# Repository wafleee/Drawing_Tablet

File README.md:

# Drawing Tablet

I am making a bluetooth drawing tablet that can send images you make on it to your computer. The main audience is people who love digital drawing but cant afford proper hardware like a Ipad and apple pencil or Large drawing pad. 

$\huge\text{Features}$
____________________________________________________________________________________________________________________________________________________________________________________________________________________________
- High quality image export (via BLE or Wifi)
- Multicolor drawing
- Save pictures to ESP32 memory
- Long battery life (3-4 hour, with continuous usage )
- Built in Stylus storage
- Large Screen (2.8 inches)

$\huge\text{Schematic}$
____________________________________________________________________________________________________________________________________________________________________________________________________________________________

The schematic is easy to understand and has neat wiring

$\huge\text{PCB Design }$
____________________________________________________________________________________________________________________________________________________________________________________________________________________________

$\huge\text{BOM }$
____________________________________________________________________________________________________________________________________________________________________________________________________________________________

$\large\text{Price in INR }$

| Ref.       | Qty | Part / Value             | LCSC #        |      Price / pc |
| ---------- | --: | ------------------------ | ------------- | --------------: |
| BT2        |   1 | JST-PH 2-pin             | **C265016**   |           ₹6.41 |
| C1, C4     |   2 | 4.7 µF                   | **C915849**   |          ₹56.46 |
| C5         |   1 | 10 µF                    | **C111896**   |          ₹78.10 |
| C6         |   1 | 0.1 µF                   | **C106148**   |          ₹11.42 |
| C7, C8     |   2 | 1 µF                     | **C91185**    |           ₹3.55 |
| D1, D2, D3 |   3 | Indicator LED            | **C125084**   |           ₹3.95 |
| IC1        |   1 | NCP186 3.3 V LDO         | **C719823**   |          ₹32.75 |
| J1         |   1 | 1×14 female socket       | **C2905420**  |          ₹14.69 |
| J2         |   1 | 1×5 male header          | **C55629812** |           ₹3.69 |
| J3         |   1 | USB-C USB 2.0 receptacle | **C3025063**  |          ₹98.75 |
| R1, R2, R6 |   3 | 470 Ω                    | **C114564**   |           ₹0.51 |
| R3, R4     |   2 | 10 kΩ                    | **C84376**    |           ₹0.63 |
| R5, R10    |   2 | 5.1 kΩ                   | **C728389**   |          ₹2.14  |
| R7         |   1 | 1.5 kΩ                   | **C309587**   |           ₹1.52 |
| R8, R9     |   2 | 10 kΩ                    | **C84376**    |           ₹0.63 |
| SW3, SW4   |   2 | Push button              | **C318884**   |           ₹1.98 |
| U1         |   1 | ESP32-S3-MINI-1-N4       | **C2847294**  |           ₹ 369 |
| U4         |   1 | USB ESD protection       | **C94934**    |          ₹51.26 |
| U5         |   1 | MCP73871                 | **C144351**   |         ₹456.94 |

$\huge\text{Firmware}$

You do not have to add any external software. Just upload the code to the board using a cable and the Arduino ide software will handle everything else.

$\huge\text{CREDITS }$
____________________________________________________________________________________________________________________________________________________________________________________________________________________________

FUSION 360 - https://www.autodesk.com/in/products/fusion-360/overview

KICAD - https://www.kicad.org/

Arduino IDE - https://www.arduino.cc/en/software/

$\large\text{FIRMWARE CREDITS  }$

SPI.h

TFT_eSPI.h  By Bodmer 

Bluetoothserial.h

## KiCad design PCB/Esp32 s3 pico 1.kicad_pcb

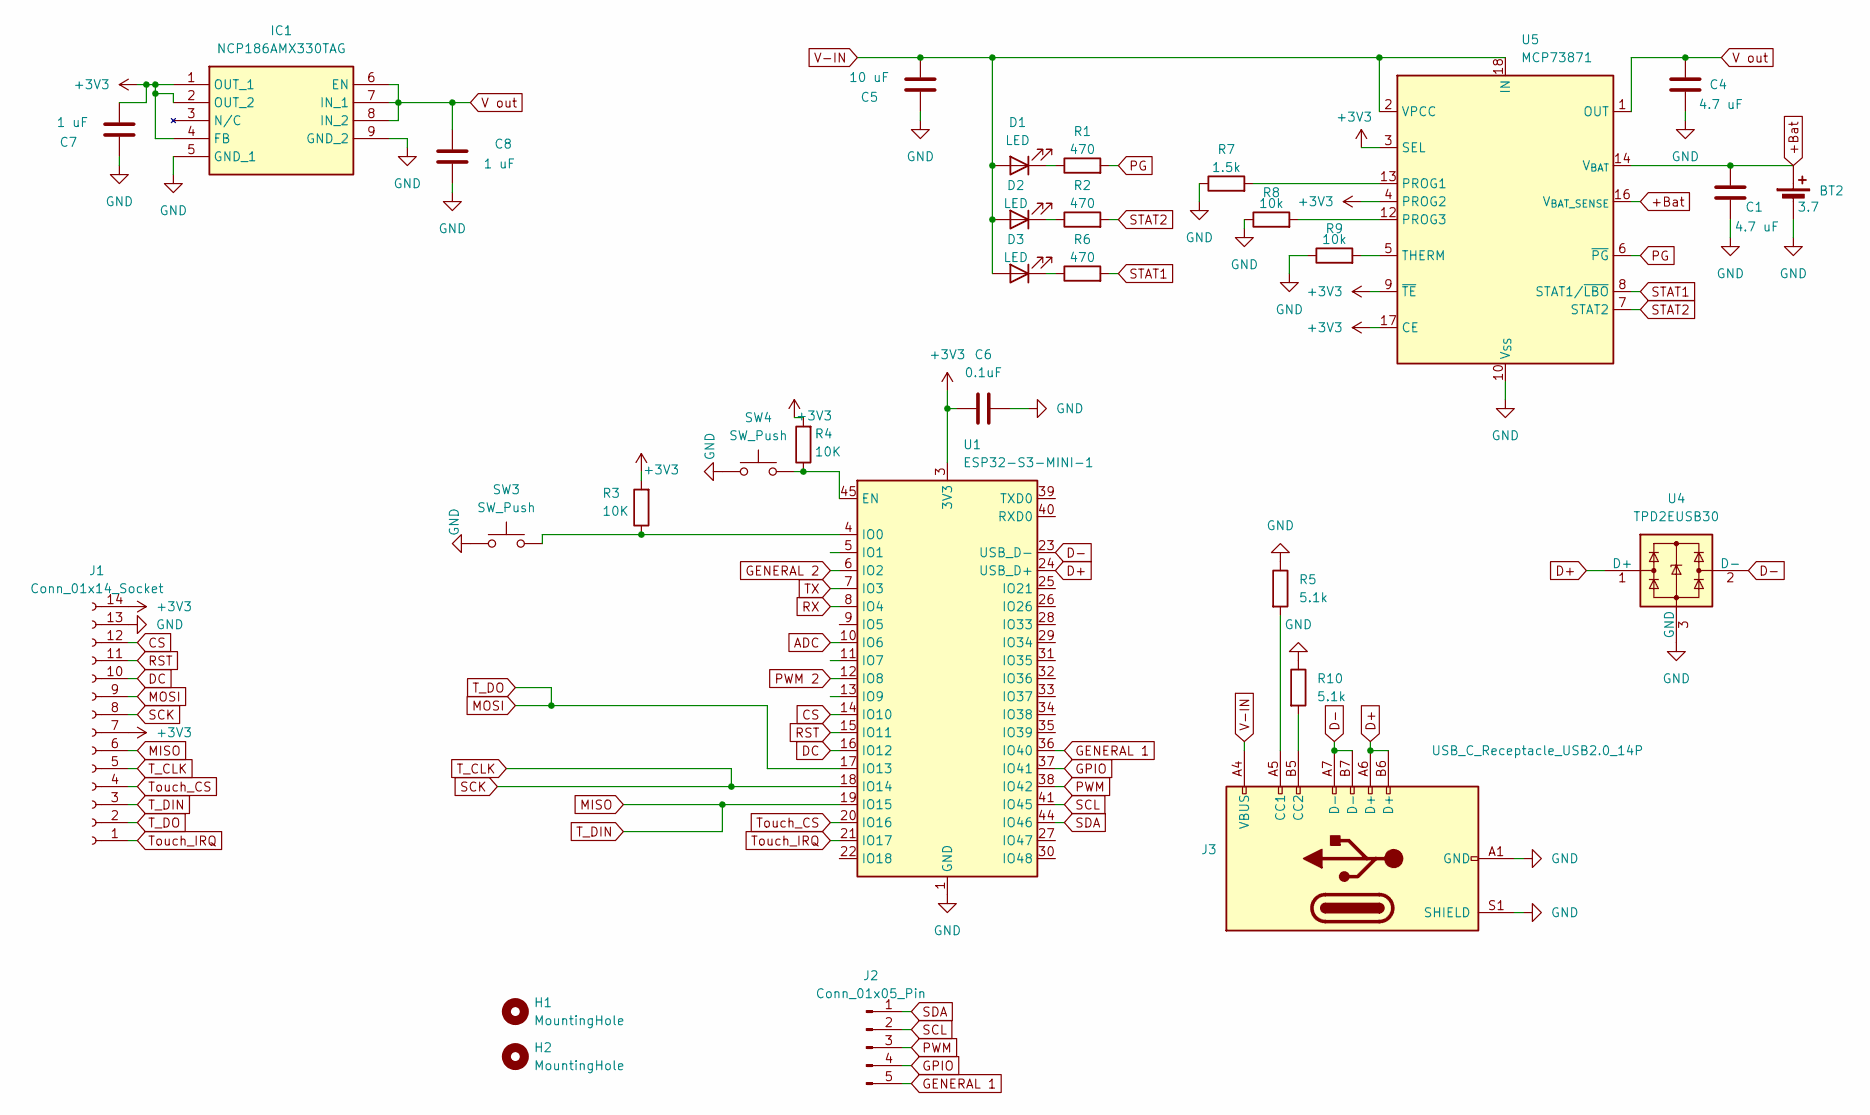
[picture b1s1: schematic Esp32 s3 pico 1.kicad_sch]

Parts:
BT2: 3.7; JST_PH_S2B-PH-K_1x02_P2.00mm_Horizontal
C1, C4: 4.7 uF; C_1812_4532Metric_Pad1.57x3.40mm_HandSolder
C5: 10 uF; C_1812_4532Metric_Pad1.57x3.40mm_HandSolder
C6: 0.1uF; C_1812_4532Metric_Pad1.57x3.40mm_HandSolder
C7, C8: 1 uF; C_0805_2012Metric
D1, D2, D3: LED; LED_1210_3225Metric
H1, H2: MountingHole; MountingHole_3.2mm_M3
IC1: NCP186AMX330TAG; Mouser Part Number 863-NCP186AMX330TAG
J1: Conn_01x14_Socket; PinSocket_1x14_P2.54mm_Vertical
J2: Conn_01x05_Pin; PinHeader_1x05_P2.54mm_Vertical
J3: USB_C_Receptacle_USB2.0_14P; USB_C_Receptacle_GCT_USB4105-xx-A_16P_TopMnt_Horizontal
R1, R2, R6: 470; R_0805_2012Metric_Pad1.20x1.40mm_HandSolder
R3, R4: 10K; R_0805_2012Metric_Pad1.20x1.40mm_HandSolder
R5, R10: 5.1k; R_1210_3225Metric
R7: 1.5k; R_1210_3225Metric
R8, R9: 10k; R_0805_2012Metric_Pad1.20x1.40mm_HandSolder
SW3, SW4: SW_Push; SW_SPST_CK_RS282G05A3
U1: ESP32-S3-MINI-1; ESP32-S2-MINI-1
U4: TPD2EUSB30; Texas_DRT-3
U5: MCP73871; QFN-20-1EP_4x4mm_P0.5mm_EP2.5x2.5mm

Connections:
+3V3: C6.1, C7.2, IC1.1 (OUT_1), IC1.2 (OUT_2), IC1.4 (FB), J1.7, J1.14, R3.2, R4.2, U1.3 (3V3), U5.3 (SEL), U5.4 (PROG2), U5.9 (~TE), U5.17 (CE)
+Bat: BT2.1 (+), C1.1, U5.14 (V_{BAT}), U5.15 (V_{BAT}), U5.16 (V_{BAT_SENSE})
ADC: U1.10 (IO6)
CS: J1.12, U1.14 (IO10)
D+: J3.A6 (D+), J3.B6 (D+), U1.24 (USB_D+), U4.1 (D+)
D-: J3.A7 (D-), J3.B7 (D-), U1.23 (USB_D-), U4.2 (D-)
DC: J1.10, U1.16 (IO12)
GENERAL 1: J2.5, U1.36 (IO40)
GENERAL 2: U1.6 (IO2)
GND: BT2.2 (-), C1.2, C4.2, C5.1, C6.2, C7.1, C8.2, IC1.5 (GND_1), IC1.9 (GND_2), J1.13, J3.A1 (GND), J3.A12 (GND), J3.B1 (GND), J3.B12 (GND), J3.S1 (SHIELD), R5.1, R7.1, R8.1, R9.1, R10.1, SW3.1, SW4.1, U1.1 (GND), U1.2 (GND), U1.42 (GND), U1.43 (GND), U1.46 (GND), U1.47 (GND), U1.48 (GND), U1.49 (GND), U1.50 (GND), U1.51 (GND), U1.52 (GND), U1.53 (GND), U1.54 (GND), U1.55 (GND), U1.56 (GND), U1.57 (GND), U1.58 (GND), U1.59 (GND), U1.60 (GND), U1.61 (GND), U1.62 (GND), U1.63 (GND), U1.64 (GND), U1.65 (GND), U4.3 (GND), U5.10 (V_{SS}), U5.11 (V_{SS}), U5.21 (V_{SS})
GPIO: J2.4, U1.37 (IO41)
MISO: J1.3, J1.6, U1.19 (IO15)
MOSI: J1.2, J1.9, U1.17 (IO13)
unnamed: D1.1 (K), R1.1
unnamed: D2.1 (K), R2.1
unnamed: D3.1 (K), R6.1
unnamed: J3.A5 (CC1), R5.2
unnamed: J3.B5 (CC2), R10.2
unnamed: R4.1, SW4.2, U1.45 (EN)
unnamed: R3.1, SW3.2, U1.4 (IO0)
unnamed: R7.2, U5.13 (PROG1)
unnamed: R8.2, U5.12 (PROG3)
unnamed: R9.2, U5.5 (THERM)
PG: R1.2, U5.6 (~PG)
PWM: J2.3, U1.38 (IO42)
PWM 2: U1.12 (IO8)
RST: J1.11, U1.15 (IO11)
RX: U1.8 (IO4)
SCK: J1.5, J1.8, U1.18 (IO14)
SCL: J2.2, U1.41 (IO45)
SDA: J2.1, U1.44 (IO46)
STAT1: R6.2, U5.8 (STAT1/~LBO)
STAT2: R2.2, U5.7 (STAT2)
TX: U1.7 (IO3)
Touch_CS: J1.4, U1.20 (IO16)
Touch_IRQ: J1.1, U1.21 (IO17)
V out: C4.1, C8.1, IC1.6 (EN), IC1.7 (IN_1), IC1.8 (IN_2), U5.1 (OUT), U5.20 (OUT)
V-IN: C5.2, D1.2 (A), D2.2 (A), D3.2 (A), J3.A4 (VBUS), J3.A9 (VBUS), J3.B4 (VBUS), J3.B9 (VBUS), U5.2 (VPCC), U5.18 (IN), U5.19 (IN)

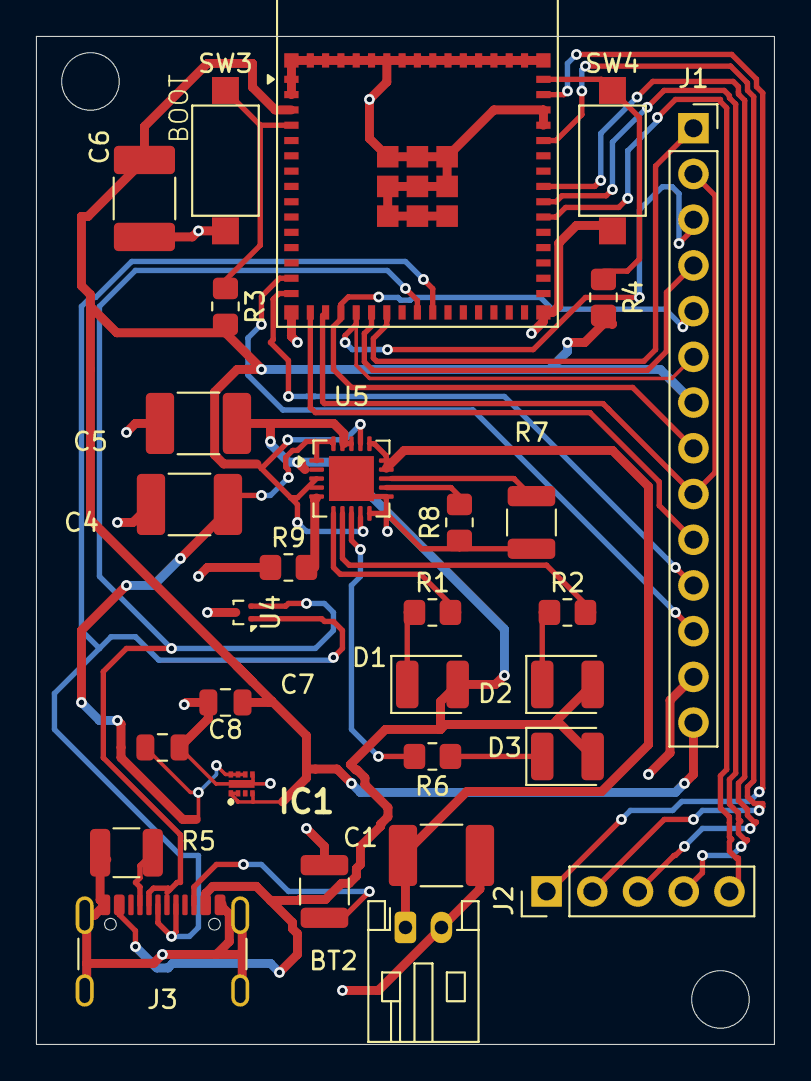
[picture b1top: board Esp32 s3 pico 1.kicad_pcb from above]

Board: 2 copper layers, 41.0 x 56.0 mm, 31 parts (0 on the bottom side), 33 nets.
